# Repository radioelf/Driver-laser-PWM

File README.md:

# Driver-laser-PWM
Driver for the control of a small power laser through PWM (GRBL)

Driver para el control de potencia de pequeños láseres a través de PWM y control de temperatura

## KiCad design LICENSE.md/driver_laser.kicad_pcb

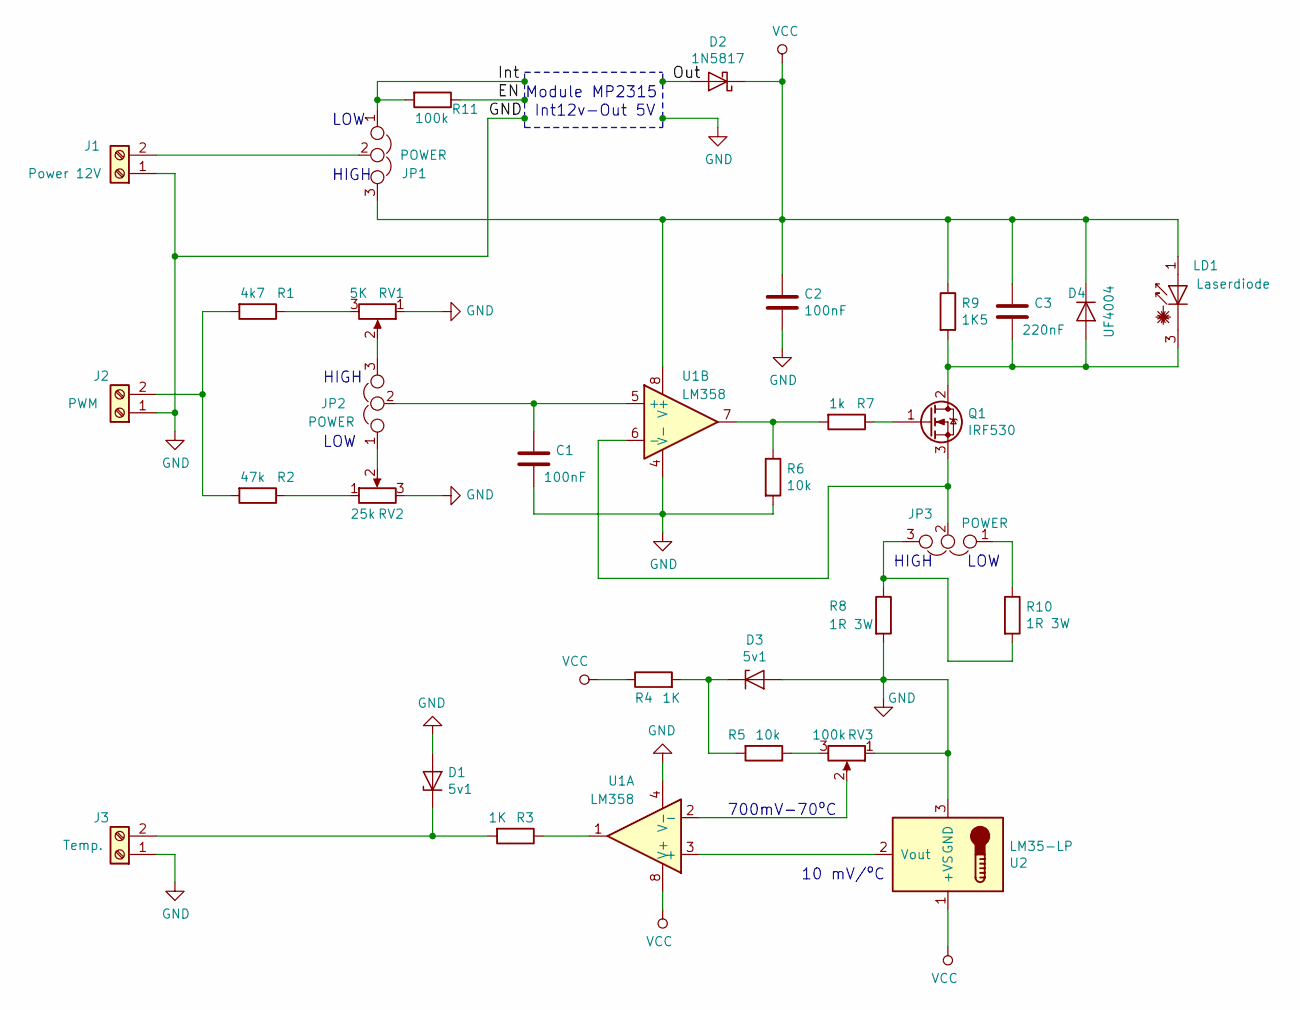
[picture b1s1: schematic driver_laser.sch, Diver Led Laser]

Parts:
C1, C2: 100nF; C_Disc_D3.0mm_W1.6mm_P2.50mm
C3: 220nF; C_Rect_L7.0mm_W2.0mm_P5.00mm
D1, D3: 5v1; D_A-405_P7.62mm_Horizontal
D2: 1N5817; D_A-405_P10.16mm_Horizontal
D4: UF4004; D_A-405_P10.16mm_Horizontal
J1: Power 12V; TerminalBlock_4UCON_19963_02x3.5mm_Straight
J2: PWM; TerminalBlock_4UCON_19963_02x3.5mm_Straight
J3: Temp.; TerminalBlock_4UCON_19963_02x3.5mm_Straight
JP1, JP2, JP3: POWER; Pin_Header_Straight_1x03_Pitch2.54mm
LD1: Laserdiode; Pin_Header_Straight_2x01_Pitch2.00mm
Q1: IRF530; TO-220-3_Vertical
R1: 4k7; R_Axial_DIN0204_L3.6mm_D1.6mm_P7.62mm_Horizontal
R2: 47k; R_Axial_DIN0204_L3.6mm_D1.6mm_P7.62mm_Horizontal
R3, R4: 1K; R_Axial_DIN0204_L3.6mm_D1.6mm_P7.62mm_Horizontal
R5, R6: 10k; R_Axial_DIN0204_L3.6mm_D1.6mm_P7.62mm_Horizontal
R7: 1k; R_Axial_DIN0204_L3.6mm_D1.6mm_P7.62mm_Horizontal
R8, R10: 1R 3W; R_Axial_DIN0414_L11.9mm_D4.5mm_P20.32mm_Horizontal
R9: 1K5; R_Axial_DIN0204_L3.6mm_D1.6mm_P7.62mm_Horizontal
R11: 100k; R_Axial_DIN0204_L3.6mm_D1.6mm_P7.62mm_Horizontal
RV1: 5K; Potentiometer_Trimmer_Bourns_3266W
RV2: 25k; Potentiometer_Trimmer_Bourns_3266W
RV3: 100k; Potentiometer_Trimmer_Bourns_3266W
U1: LM358; DIP-8_W7.62mm
U2: LM35-LP; TO-92_Rugged_Reverse

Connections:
/EN: R11.1; also elsewhere on the board
/Int: JP1.1, R11.2; also elsewhere on the board
/Out: D2.2 (A); also elsewhere on the board
GND: C1.2, C2.2, D1.2 (A), D3.2 (A), J1.1, J2.1, J3.1, R6.2, R8.2, RV1.1, RV2.3, RV3.1, U1.4 (V-), U2.3 (GND); also elsewhere on the board
unnamed: C1.1, JP2.2, U1.5 (+)
unnamed: C3.2, D4.2 (A), LD1.3 (K), Q1.2 (D), R9.2
unnamed: D1.1 (K), J3.2, R3.2
unnamed: D3.1 (K), R4.2, R5.2
unnamed: J1.2, JP1.2
unnamed: J2.2, R1.2, R2.2
unnamed: JP2.1, RV2.2
unnamed: JP2.3, RV1.2
unnamed: JP3.1, R10.1
unnamed: JP3.2, Q1.3 (S), U1.6 (-)
unnamed: JP3.3, R8.1, R10.2
unnamed: Q1.1 (G), R7.1
unnamed: R1.1, RV1.3
unnamed: R2.1, RV2.1
unnamed: R3.1, U1.1
unnamed: R5.1, RV3.3
unnamed: R6.1, R7.2, U1.7
unnamed: RV3.2, U1.2 (-)
unnamed: U1.3 (+), U2.2 (Vout)
VCC: C2.1, C3.1, D2.1 (K), D4.1 (K), JP1.3, LD1.1 (A), R4.1, R9.1, U1.8 (V+), U2.1 (+VS)

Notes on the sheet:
Module MP2315
Int12v-Out 5V
LOW
HIGH
10 mV/ºC
700mV-70ºC

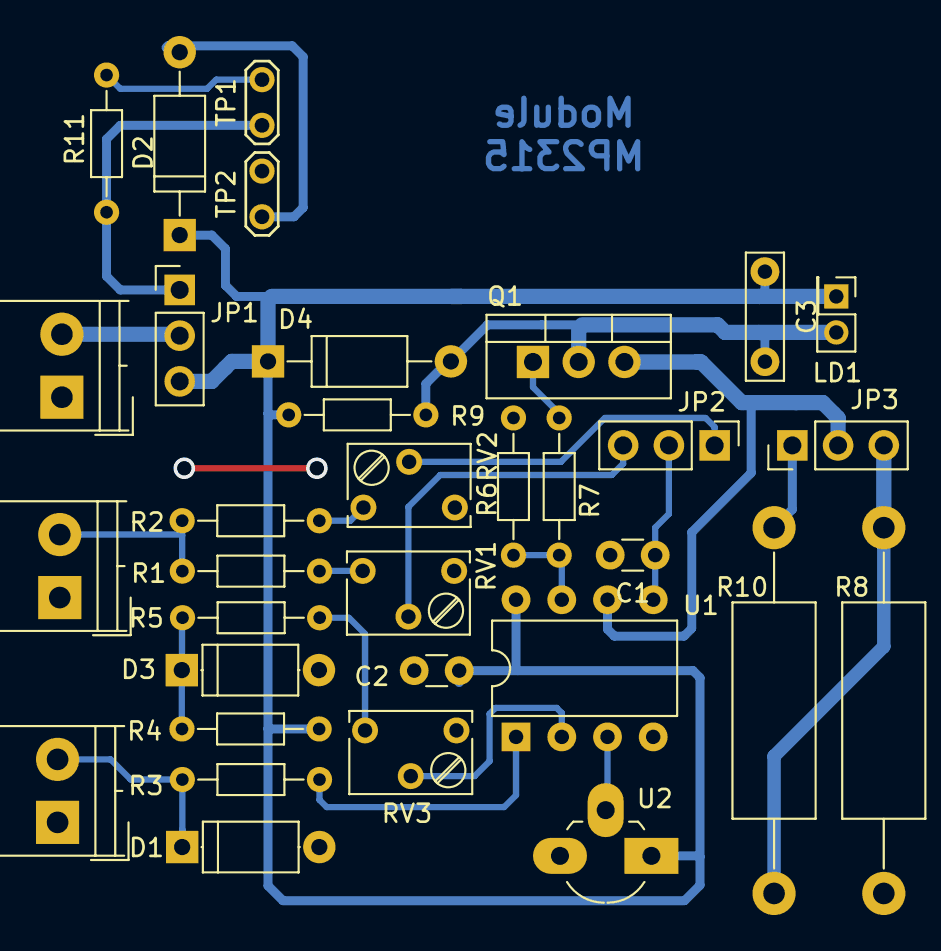
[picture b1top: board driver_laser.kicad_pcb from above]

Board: 2 copper layers, 33 parts (0 on the bottom side), 24 nets.

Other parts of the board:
TP1: Int12V; Test_Point_2Pads
TP2: Out5V; Test_Point_2Pads

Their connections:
/EN: TP1.2; also elsewhere on the board
/Int: TP1.1; also elsewhere on the board
/Out: TP2.1; also elsewhere on the board
GND: TP2.2; also elsewhere on the board
